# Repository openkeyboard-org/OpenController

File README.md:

# OpenController

OpenController is an open-source wireless keyboard controller designed to be compatible with OpenDongle.

## Firmware

The first firmware target is the WCH CH592F wireless module: a keyboard-side
2.4 GHz link (pairing, connected-mode hopping, HID uplink, persistent
bonding) driven by the keyboard's host MCU over UART, bench-validated
against OpenDongle. See [firmware/README.md](./firmware/README.md) for
toolchain, build, and flashing instructions.

## Hardware

The first hardware implementation is a 10.16 mm x 20.5 mm castellated WCH
CH572D module with OpenDongle's PCB antenna, soldered onto the keyboard PCB
beside the host MCU. It is a first revision that has not been built yet. See [hardware/README.md](./hardware/README.md).

## Repository layout

- `firmware/` — firmware source and related software artifacts.
- `hardware/` — hardware design files and documentation.
- `third_party/` — pinned git submodules used by the firmware.
- `tools/` — development and support tooling.

## Licensing

- Firmware and tools software: [Apache License 2.0](./firmware/LICENSE).
- Hardware designs: [CERN Open Hardware Licence Version 2 - Weakly Reciprocal](./hardware/LICENSE).
- The submodules under `third_party/` contain third-party code under their
  own terms; firmware dependency and derived-file provenance is recorded in
  [`firmware/NOTICE`](./firmware/NOTICE).

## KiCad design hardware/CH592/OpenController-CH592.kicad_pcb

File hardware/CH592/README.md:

# OpenController CH592

OpenController CH592 is a 10.16 mm x 20.5 mm castellated 2.4 GHz wireless module for keyboards, built around the WCH CH592D RISC-V BLE MCU. It has the same outline, castellated pinout, PCB antenna, and 0.8 mm stackup as the [CH572](../CH572/) module, so a host PCB laid out for one takes the other. Like the CH572, it uses the independently created, WCH-informed PCB antenna from [OpenDongle](https://github.com/openkeyboard-org/OpenDongle).

This is the first CH592 revision and no boards have been built yet. The existing OpenController firmware targets the CH592F; it needs a CH592D board profile for this module (see [Known issues](#known-issues-and-next-revision)).

## Design files

| File or directory | Purpose |
| --- | --- |
| `OpenController-CH592.kicad_pro` | KiCad 10 project and design-rule settings |
| `OpenController-CH592.kicad_sch` | Schematic |
| `OpenController-CH592.kicad_pcb` | PCB layout |
| `lib/OpenController.kicad_sym` | Project-owned CH592D symbol |
| `lib/OpenController.pretty/` | Castellated-edge and CH592D QFN-20 footprints drawn for this project, and the antenna footprint copied unchanged from OpenDongle (see [`../NOTICE`](../NOTICE)) |
| `sym-lib-table`, `fp-lib-table` | Portable project-local library configuration |
| `fab/` | Exported outputs: schematic PDF and gerber/NC drill set (see [Fabrication outputs](#fabrication-outputs)) |

Open the project with KiCad 10 or later. The project-owned symbol and footprints resolve through `${KIPRJMOD}` paths in the local library tables. The remaining parts (passives, inductor, crystal, LDO, connector symbol) come from KiCad 10's standard libraries. The schematic and board carry embedded copies of every symbol and footprint, so they open without those libraries, but updating parts from the library needs them installed.

## Host interface

J1 is nine castellated half-holes (1.0 mm drill), three on each of three edges, all on one 0.1 in (2.54 mm) grid so a host can also use standard 0.1 in pin headers. Viewed from the top with the antenna at the bottom, pad 1 is the uppermost pad on the left edge, and the numbering runs counter-clockwise: down the left edge (1-3), up the right edge (4-6), then right to left along the top (7-9). The top silkscreen dot marks pad 1. Pad positions and functions match the CH572 module, except that the CH592D has no reset pin and its USB pins are separate from SWD.

| Pad | Edge | Signal | CH592D pin | Direction | Notes |
| ---: | --- | --- | --- | --- | --- |
| 1 | Left, top | GND | EP | - | |
| 2 | Left, middle | UART_TX | PB13 (8) | out | TXD1 on the UART1 remap, as used by the firmware and OpenBoot |
| 3 | Left, bottom | UART_RX | PB12 (9) | in | RXD1 on the UART1 remap |
| 4 | Right, bottom | NRST | - | - | Not connected: the CH592D has no reset pin |
| 5 | Right, middle | VCC | - | in | 3.3 V to 6.0 V supply into the LDO |
| 6 | Right, top | GND | EP | - | |
| 7 | Top, right | SWDIO | PB14 (7) | bidir | Two-wire debug data (TIO) |
| 8 | Top, middle | SWCLK | PB15 (6) | in | Two-wire debug clock (TCK), also the ROM ISP strap; do not hold low at power-up |
| 9 | Top, left | WAKE | PA11 (1) | out | Host wake line |

The board is 10.16 mm (0.4 in) wide, so the two side rows sit 0.4 in apart. Measured to the hole centres, the top pads are 2.54, 5.08, and 7.62 mm from the left edge, and the side pads are 2.54, 5.08, and 7.62 mm below the top edge. The J1 signals are 3.3 V logic and none is 5 V tolerant; VCC is the supply input and takes 3.3 V to 6.0 V into the LDO. The host PCB must keep copper, ground pour, and metal away from the antenna end of the module.

## Electrical design notes

- VCC feeds U2, a Torex XC6206P332MR-G 3.3 V LDO (pin 1 VSS, pin 2 VOUT, pin 3 VIN). C1 (1 uF) is its input capacitor. Its 6.0 V maximum input covers USB VBUS; from a 3.3 V host rail it runs in dropout, which the CH592D tolerates (1.75 V to 3.6 V supply).
- U2 feeds VIO33/VDD33 (pin 5), the CH592D's only external supply input; VDCID, VDCIA, and VINTA are internal regulator nodes fed from it. C2 (2.2 uF) sits at pin 5 and is both the VDD33 capacitor the datasheet asks for with the DC-DC enabled (2.2 uF or 1 uF) and the LDO output capacitor. OpenDongle CH592 likewise uses a single capacitor there.
- The internal DC-DC converter is fitted. VSW (pin 4) drives L1 (10 uH, the datasheet's recommended value) into VDCID (pin 3). C4 (4.7 uF, the recommended value) decouples VDCID, and VDCIA (pin 16) is tied to VDCID as the datasheet recommends. C5 (470 nF) decouples VINTA (pin 14).
- The DC-DC is off at power-on. The CH592D then supplies VSW directly from VDD33, and L1 passes it through to VDCID. The firmware's `opencontroller-ch592` profile turns the converter on (`KBD_DCDC_ENABLE := 1`). WCH puts the operating current with the DC-DC running at about 60% of the direct-supply figure. OpenDongle CH592 makes the opposite choice: it leaves the DC-DC off and ties VSW straight to VDCID.
- JLC has no Basic inductor suited to the DC-DC: its Basic 10 uH parts (C1035, C1046) are signal inductors rated 3 mA and 15 mA. L1 is a TDK MLZ1608M100WT000, a 0603 multilayer inductor made for DC-DC power lines, with 1.05 ohm DCR and a 90 mA rating in the JLC listing.
- Y1 is a 32 MHz, 8 pF-load crystal on X32MI/X32MO (pins 13 and 12), the same part as the CH572 module. No external load capacitors are fitted; the CH592 provides programmable internal load capacitance (`R8_XT32M_TUNE`), and OpenDongle CH592 also runs an 8 pF crystal on it.
- The RF output (ANT, pin 15) drives the PCB antenna directly, as on OpenDongle.
- GND reaches the CH592D only through the exposed pad (pin 21 in the footprint), which has four 0.6/0.2 mm thermal vias to the bottom ground plane.
- U1's footprint was drawn for this project from the CH592 datasheet's QFN20 drawing (chapter 21: 3.0 +/- 0.1 mm body, 1.9 +/- 0.2 mm exposed pad, 0.25 +/- 0.07 mm leads). KiCad's generic `QFN-20-1EP_3x3mm_P0.4mm_EP1.65x1.65mm` would not do: its lands reach 1.025 mm from the package centre, inside the 1.05 mm edge of a maximum-size CH592D exposed pad. Here the lands run from 1.20 mm to 1.85 mm (0.65 mm x 0.2 mm), 0.15 mm clear of the largest exposed pad. On a nominal 3.0 mm body a longest lead overhangs their inner end by 0.02 mm, and by up to 0.07 mm on a smallest 2.9 mm body. The exposed-pad land is the nominal 1.9 mm. The four thermal vias are built into the footprint, 0.7 mm from the centre along each axis, near the exposed-pad corners. The exposed-pad solder paste is a central window plus four edge windows, 51% of the pad with their rounded corners, each at least 0.175 mm from the via holes, so no paste sits over a via barrel where solder could wick away. The vias are 0.6 mm pads on 0.2 mm drills, which gives the 0.20 mm annular ring JLCPCB asks of plated pad holes. On the top layer their copper merges with the exposed pad: it reaches 0.05 mm beyond the exposed-pad land, under solder mask and at least 0.2 mm from the nearest land, and the paste windows overlap its outer 0.025 mm. The vias are open on the component side, inside the exposed-pad mask opening, and tented on the bottom. TI's thermal-pad guidance (SLMA002) prefers capping them on the component side to limit solder wicking and voiding, but open vias in the exposed pad have worked in OpenKeyboard testing, so they stay open.
- The CH592D's QFN-20 package does not bond out the RST pin, so pad 4 (NRST) is not connected. Reset the module by cycling VCC or over SWD.
- PB15 is the CH592D's ROM ISP strap: held low at power-on, it starts the ROM bootloader. The boot ROM pulls PB15 up, so an open pad 8 boots normally, but a host must not hold pad 8 low during power-up. USB (PB10/PB11) is not brought out, so this module is programmed over two-wire debug rather than ROM ISP. Two-wire debug is enabled from the factory (`CFG_DEBUG_EN`, datasheet Table 2-3), so a WCH-LinkE on pads 7 and 8 programs a blank part, and OpenBoot updates the firmware over the UART after that.
- Unused GPIOs (PA10, PA12 to PA15, PB10, PB11) carry no-connect flags.
- AE1 and J1 are PCB features, not assembly parts. Their footprints are excluded from the BOM and position file.

## Layout notes

- The outline, antenna, ground pours, and via fence are the CH572 module's: the antenna sits along the bottom edge of the 10.16 mm wide board, centred with about 0.58 mm side margins, and both ground pours stop at its inner edge (y = 117.205 mm) behind a 0.5/0.2 mm via fence at 0.75 mm pitch. The two vias beside the antenna's ground pad sit 0.1 mm to 0.15 mm closer to the board edge than on the CH572 to clear the ANT trace.
- The CH592D has ANT, VINTA, X32MI, and X32MO on one side of the package. U1 follows the RF corner of OpenDongle CH592, rotated 90 degrees with the antenna: it sits where U3 sits relative to the antenna feed and via fence there, moved 0.1 mm further from the fence, so that C5 fits in the strip between U1 and the fence without the courtyards overlapping.
- The ANT trace is 0.15 mm wide and about 4.8 mm long (about 4.3 mm on OpenDongle CH592). It runs along U1's pin row and then down beside C5 to the antenna feed.
- Y1 sits at U1's corner on the antenna side. X32MI runs between it and the via fence (0.15 mm, about 7.1 mm) and X32MO into its near pad (about 3.6 mm). The crystal's two ground pads each have a via.
- L1 and C4 sit between U1 and the castellated edge, and VDCIA reaches VDCID around U1's right-hand side. C2 sits beside VDD33, and the LDO and C1 sit between them and the castellated edge.
- Only two signals use the bottom layer: SWDIO from a via at U1's left-hand side, crossing under U1 between its two rows of thermal vias, and WAKE from a via inside the VDCIA loop. Everything else on the bottom layer is ground. SWDIO runs close to the right-hand castellations, so the bottom-layer ground beside pad 6 is a separate piece that joins through pad 6 itself and a stitching via; the rest of the bottom pour is one piece.
- Each castellated pad is 1.5 mm x 3.0 mm and straddles the board edge, leaving 1.5 mm of pad on the board and a 0.25 mm annular ring along the edge. The outermost holes are 2.54 mm (centre) from the corners, so every pad edge is at least 1.79 mm from the adjacent board edge, and hole edges are 1.54 mm apart. See [Known issues](#known-issues-and-next-revision) for JLCPCB's corner guidance.

## Design rules

The board-setup constraints are set to JLCPCB's 1-2 layer, 1 oz capabilities, as on the CH572. The design itself uses larger values (0.2 mm default track and clearance, 0.5/0.2 mm vias).

| Constraint | Setting |
| --- | --- |
| Minimum clearance / track width | 0.10 mm / 0.10 mm |
| Minimum via diameter / annular ring | 0.25 mm / 0.05 mm |
| Minimum through hole | 0.15 mm |
| Hole to hole / hole to copper | 0.20 mm / 0.20 mm |
| Copper to board edge | 0.20 mm (castellated pads are exempt) |
| Silkscreen text height / thickness | 1.0 mm / 0.15 mm |
| Solder mask minimum web | 0.10 mm, 1:1 expansion |

KiCad's board setup has a single hole-to-hole minimum, a single annular-ring minimum (set to JLCPCB's 0.05 mm via value), and no pad-to-silkscreen minimum, so three JLCPCB limits are not checked by DRC: 0.45 mm between plated pad holes, a 0.20 mm annular ring on plated pad holes, and 0.15 mm from pads to silkscreen. The layout meets all three: the closest plated pad holes are U1's thermal vias, 1.2 mm apart edge to edge (the castellations are 1.54 mm apart); the thermal vias have a 0.20 mm ring and the castellations 0.25 mm; and silkscreen stays at least 0.2 mm from every pad opening.

## Design verification

```sh
kicad-cli sch erc --severity-all OpenController-CH592.kicad_sch
kicad-cli pcb drc --severity-all --schematic-parity OpenController-CH592.kicad_pcb
```

ERC reports 0 errors and 0 warnings. DRC reports 0 violations, 0 unconnected items, and 0 schematic parity issues.

## Fabrication outputs

`fab/` holds the exported outputs: the schematic as PDF, and the gerber/NC drill set under `fab/gerbers/`. The KiCad sources remain the design of record; regenerate the exports with KiCad 10 whenever the schematic or layout changes:

```sh
kicad-cli sch export pdf -o fab/OpenController-CH592-schematic.pdf OpenController-CH592.kicad_sch
kicad-cli pcb export gerbers -o fab/gerbers/ \
    -l F.Cu,B.Cu,F.Paste,B.Paste,F.Silkscreen,B.Silkscreen,F.Mask,B.Mask,Edge.Cuts \
    --no-protel-ext --check-zones OpenController-CH592.kicad_pcb
kicad-cli pcb export drill -o fab/gerbers/ --excellon-separate-th \
    --generate-map --map-format gerberx2 OpenController-CH592.kicad_pcb
```

The gerber job file reports 10.21 mm x 20.55 mm and 0.84 mm. The size includes the outline's 0.05 mm line width and the thickness includes both 0.02 mm solder mask layers. Order the board as 10.16 mm x 20.5 mm and 0.8 mm.

Anyone ordering from these files must still pass the stackup, castellation, and antenna requirements below to the fabricator; the gerbers alone do not carry them. JLC-oriented assembly outputs from the Fabrication Toolkit plugin go to `production/`, which stays untracked.

## Fabrication requirements

The antenna is only tuned for this construction. Use these settings unless a revised PCB has been validated:

| Parameter | Requirement |
| --- | --- |
| Layer count | 2 copper layers |
| Finished board size | 10.16 mm x 20.5 mm |
| Finished thickness | 0.8 mm nominal (35 um + 0.73 mm core + 35 um) |
| Material | FR-4 |
| Copper | 1 oz / 35 um outer copper |
| Castellated holes | Yes, on three edges (9 half-holes, 1.0 mm) |
| Surface finish | ENIG recommended for the castellated pads |
| Minimum finished drill | 0.20 mm |
| Minimum track/space used | 0.15 mm track, 0.2 mm clearance |
| Soldermask | Both sides; no soldermask over the castellated pads or antenna conductor |

Preserve the antenna copper, ground edge, board thickness, and via fence exactly, and do not let the fabricator add serial numbers or tooling features in the antenna region. The enclosure and host PCB must not place metal or a ground pour over or directly under the antenna.

## Suggested BOM

The listed LCSC/JLCPCB numbers are suggested assembly parts, not sole-source requirements. Library type is as JLCPCB listed it on 2026-10-25.

| References | Qty | Value / part | Package | Suggested LCSC part | JLC library | Notes |
| --- | ---: | --- | --- | --- | --- | --- |
| U1 | 1 | WCH CH592D | QFN-20, 3 mm x 3 mm, 0.4 mm pitch, exposed pad | C41417128 | Extended | Same part as OpenDongle CH592. Confirm pin-1 orientation and exposed-pad soldering |
| U2 | 1 | Torex XC6206P332MR-G, 3.3 V LDO | SOT-23-3 | C5446 | Basic | 200 mA, 6.0 V maximum input |
| L1 | 1 | 10 uH, TDK MLZ1608M100WT000 | 0603 | C76798 | Extended | DC-DC inductor; JLC's Basic 10 uH parts are 3 mA and 15 mA signal inductors |
| Y1 | 1 | 32 MHz crystal | 2016, 4 pad | C37635332 | Extended | 8 pF load, +/-10 ppm, 40 ohm maximum ESR; same part as the CH572 module. JLC lists no Basic 32 MHz crystal |
| C1 | 1 | 1 uF | 0603 | C15849 | Basic | X5R, 50 V |
| C2 | 1 | 2.2 uF | 0603 | C23630 | Basic | X5R, 16 V |
| C4 | 1 | 4.7 uF | 0603 | C19666 | Basic | X5R, 16 V |
| C5 | 1 | 470 nF | 0603 | C1623 | Basic | X7R, 25 V |

AE1 (PCB antenna) and J1 (castellated edge) are PCB features, not assembly parts.

## Known issues and next revision

- JLCPCB's [castellated PCB design guide](https://jlcpcb.com/blog/castellated-pcbs-introduction-and-design-requirements) recommends at least 3.0 mm (5.0 mm preferred) from a castellated hole to a board corner; the outermost holes here are 2.54 mm (centre) from the corners. That row appears only in the guide's expanded table, not on JLCPCB's capabilities page or in its Chinese design guide, and JLCPCB has built castellated boards with corner holes closer than this. Select castellated holes on three edges when ordering, and expect at most an engineering query.
- The antenna's ground plane is about 10.16 mm x 17 mm here against roughly 10 mm x 13 mm on OpenDongle, and the ANT trace is about 0.5 mm longer than OpenDongle CH592's. Check the match and range on the first boards, soldered to a representative host PCB.
- With VCC at 3.3 V the LDO has almost no headroom. Torex's usage notes ask for stability testing in that condition, so check it on the first boards if hosts will feed the module from a 3.3 V rail.
- The firmware has no CH592D board profile yet. The `opencontroller-ch592` profile already matches this module's UART1 remap (PB13/PB12) and fitted DC-DC inductor. Host wake needs firmware work: the firmware drives its wake line only on PB13, and its boot-time pin park pulls PA11 up until a driver claims it. A profile for this module must drive WAKE on PA11 and leave it out of the park.

## Source attribution

- The 0.8 mm FR-4 antenna footprint is copied from OpenDongle, where it was independently created, informed by the WCH reference antenna published in the [openwch schematic/PCB library](https://github.com/openwch/schpcb_lib); no WCH CAD or artwork file was copied, imported, converted, or traced.

## License

This hardware design, including the antenna implementation described in [`../NOTICE`](../NOTICE), is licensed under the CERN Open Hardware Licence Version 2 - Weakly Reciprocal. See [`LICENSE`](LICENSE).

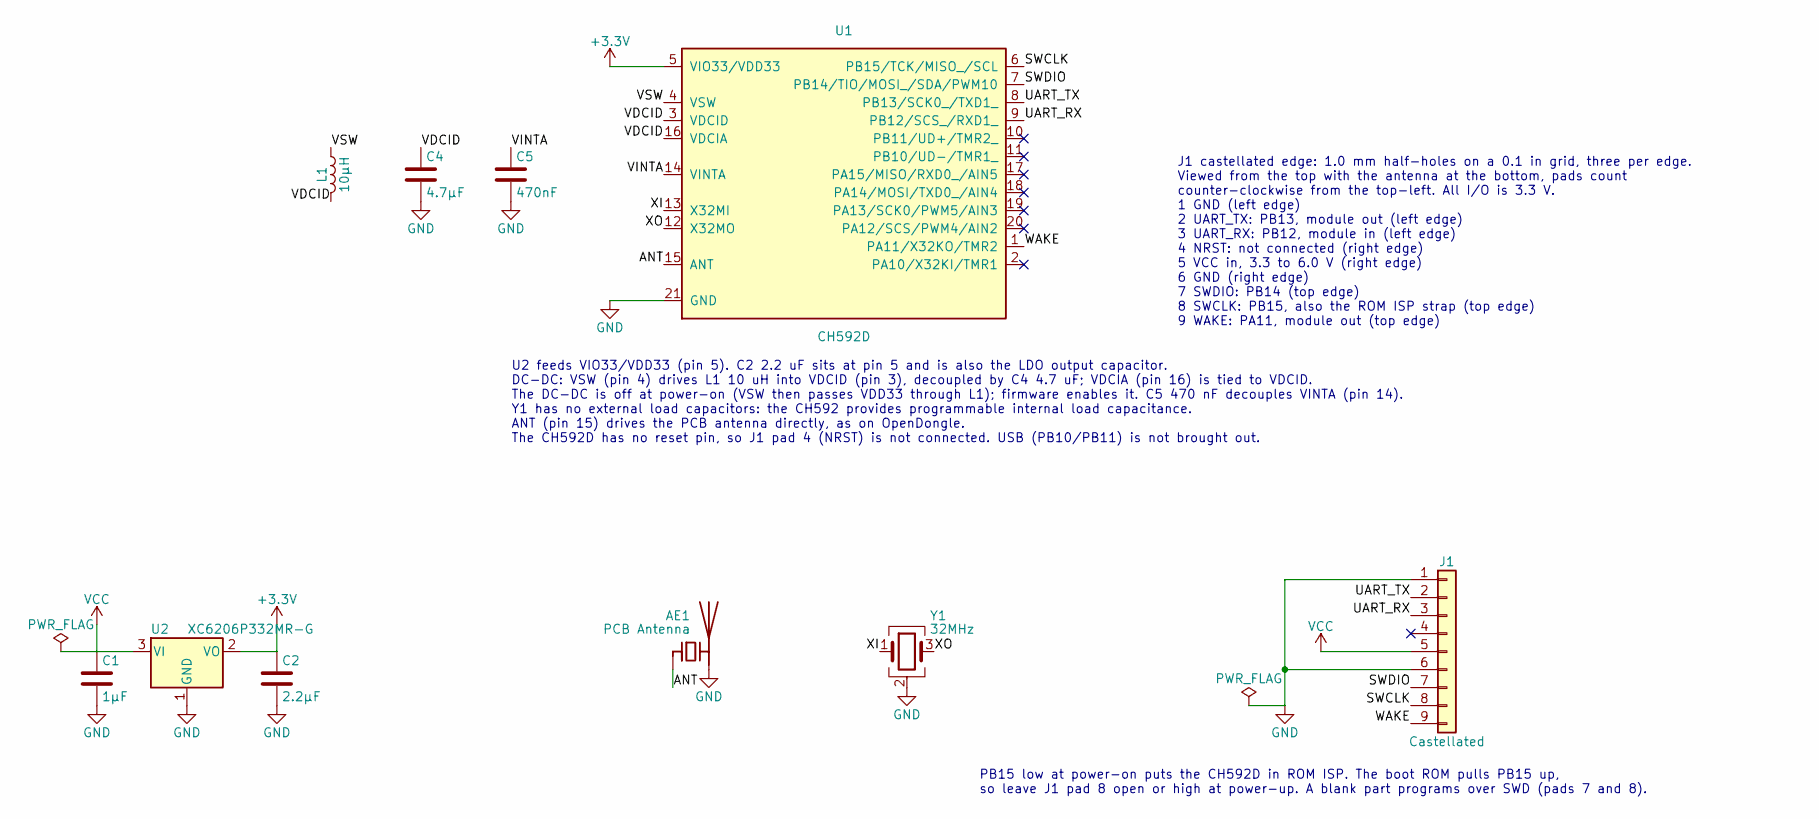
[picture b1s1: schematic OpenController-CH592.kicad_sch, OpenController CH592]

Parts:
AE1: PCB Antenna; ANT-F-2-2.4G-0.8MM-FR4-WCH
C1: 1µF; C_0603_1608Metric; LCSC C15849
C2: 2.2µF; C_0603_1608Metric; LCSC C23630
C4: 4.7µF; C_0603_1608Metric; LCSC C19666
C5: 470nF; C_0603_1608Metric; LCSC C1623
J1: Castellated; Castellated_CH592_10.16x20.5mm
L1: 10µH; L_0603_1608Metric; LCSC C76798
U1: CH592D; QFN-20-1EP_3x3mm_P0.4mm_EP1.9x1.9mm_ThermalVias; LCSC C41417128
U2: XC6206P332MR-G; SOT-23-3; LCSC C5446
Y1: 32MHz; Crystal_SMD_2016-4Pin_2.0x1.6mm; LCSC C37635332

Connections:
+3.3V: C2.1, U1.5 (VIO33/VDD33), U2.2 (VO)
/ANT: AE1.1 (FEED), U1.15 (ANT)
/SWCLK: J1.8, U1.6 (PB15/TCK/MISO_/SCL)
/SWDIO: J1.7, U1.7 (PB14/TIO/MOSI_/SDA/PWM10)
/UART_RX: J1.3, U1.9 (PB12/SCS_/RXD1_)
/UART_TX: J1.2, U1.8 (PB13/SCK0_/TXD1_)
/VDCID: C4.1, L1.2, U1.3 (VDCID), U1.16 (VDCIA)
/VINTA: C5.1, U1.14 (VINTA)
/VSW: L1.1, U1.4 (VSW)
/WAKE: J1.9, U1.1 (PA11/X32KO/TMR2)
/XI: U1.13 (X32MI), Y1.1
/XO: U1.12 (X32MO), Y1.3
GND: AE1.2 (PCB_Trace), C1.2, C2.2, C4.2, C5.2, J1.1, J1.6, U1.21 (GND), U2.1 (GND), Y1.2 (G), Y1.4 (G)
VCC: C1.1, J1.5, U2.3 (VI)

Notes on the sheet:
J1 castellated edge: 1.0 mm half-holes on a 0.1 in grid, three per edge. Viewed from the top with the antenna at the bottom, pads count counter-clockwise from the top-left. All I/O is 3.3 V. 1 GND (left edge) 2 UART_TX: PB13, module out (left edge) 3 UART_RX: PB12, module in (left edge) 4 NRST: not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
PB15 low at power-on puts the CH592D in ROM ISP. The boot ROM pulls PB15 up, so leave J1 pad 8 open or high at power-up. A blank part programs over SWD (pads 7 and 8).
U2 feeds VIO33/VDD33 (pin 5). C2 2.2 uF sits at pin 5 and is also the LDO output capacitor. DC-DC: VSW (pin 4) drives L1 10 uH into VDCID (pin 3), decoupled by C4 4.7 uF; VDCIA (pin 16) is tied to VDCID. The DC-DC is off at power-on (VSW then passes VDD33 through L1); firmware enables it. C5 470 nF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

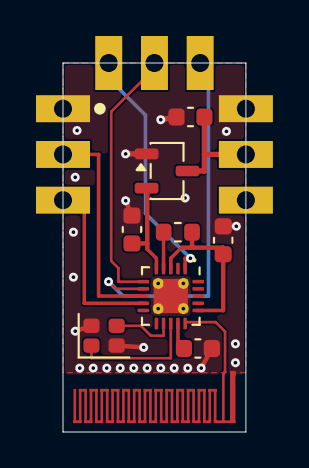
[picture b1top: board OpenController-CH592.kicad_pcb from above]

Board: 2 copper layers, 10.2 x 20.5 mm, 10 parts (0 on the bottom side), 14 nets.

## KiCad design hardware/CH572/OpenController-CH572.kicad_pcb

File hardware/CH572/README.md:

# OpenController CH572

OpenController CH572 is a 10.16 mm x 20.5 mm castellated 2.4 GHz wireless module for keyboards, built around the WCH CH572D RISC-V wireless MCU. It solders onto the keyboard PCB beside the host MCU and talks to it over UART, using the same independently created, WCH-informed PCB antenna and 0.8 mm stackup as [OpenDongle](https://github.com/openkeyboard-org/OpenDongle).

This is the first CH572 revision and no boards have been built yet. The existing OpenController firmware targets the CH592F; a CH572 port is follow-up work.

## Design files

| File or directory | Purpose |
| --- | --- |
| `OpenController-CH572.kicad_pro` | KiCad 10 project and design-rule settings |
| `OpenController-CH572.kicad_sch` | Schematic |
| `OpenController-CH572.kicad_pcb` | PCB layout |
| `lib/OpenController.kicad_sym` | Project-owned CH572D symbol |
| `lib/OpenController.pretty/` | Castellated-edge and CH572D QFN-20 footprints drawn for this project, and the antenna footprint copied unchanged from OpenDongle (see [`../NOTICE`](../NOTICE)) |
| `sym-lib-table`, `fp-lib-table` | Portable project-local library configuration |
| `fab/` | Exported outputs: schematic PDF and gerber/NC drill set (see [Fabrication outputs](#fabrication-outputs)) |

Open the project with KiCad 10 or later. The project-owned symbol and footprints resolve through `${KIPRJMOD}` paths in the local library tables. The remaining parts (passives, crystal, LDO, connector symbol) come from KiCad 10's standard libraries. The schematic and board carry embedded copies of every symbol and footprint, so they open without those libraries, but updating parts from the library needs them installed.

## Host interface

J1 is nine castellated half-holes (1.0 mm drill), three on each of three edges, all on one 0.1 in (2.54 mm) grid so a host can also use standard 0.1 in pin headers. Viewed from the top with the antenna at the bottom, pad 1 is the uppermost pad on the left edge, and the numbering runs counter-clockwise: down the left edge (1-3), up the right edge (4-6), then right to left along the top (7-9). The top silkscreen dot marks pad 1.

| Pad | Edge | Signal | CH572D pin | Direction | Notes |
| ---: | --- | --- | --- | --- | --- |
| 1 | Left, top | GND | EP | - | |
| 2 | Left, middle | UART_TX | PA3 (1) | out | Default UART TXD, as used by OpenBoot's CH57x port |
| 3 | Left, bottom | UART_RX | PA2 (20) | in | Default UART RXD |
| 4 | Right, bottom | NRST | PA8 (10) | in | Default RST pin; reset input is disabled until `CFG_RESET_EN` is set |
| 5 | Right, middle | VCC | - | in | 3.3 V to 6.0 V supply into the LDO |
| 6 | Right, top | GND | EP | - | |
| 7 | Top, right | SWDIO | PA0 (11) | bidir | Also USB D- and UART ISP |
| 8 | Top, middle | SWCLK | PA1 (12) | bidir | Also USB D+ and the ROM boot strap; 100 kOhm pull-down (R1) |
| 9 | Top, left | WAKE | PA4 (13) | out | Host wake line |

The board is 10.16 mm (0.4 in) wide, so the two side rows sit 0.4 in apart. Measured to the hole centres, the top pads are 2.54, 5.08, and 7.62 mm from the left edge, and the side pads are 2.54, 5.08, and 7.62 mm below the top edge. The J1 signals are 3.3 V logic and none is 5 V tolerant; VCC is the supply input and takes 3.3 V to 6.0 V into the LDO. The host PCB must keep copper, ground pour, and metal away from the antenna end of the module.

## Electrical design notes

- VCC feeds U2, a Torex XC6206P332MR-G 3.3 V LDO (pin 1 VSS, pin 2 VOUT, pin 3 VIN). C1 (1 uF) is its input capacitor. Its 6.0 V maximum input covers USB VBUS; from a 3.3 V host rail it runs in dropout, which the CH572 tolerates (2.0 V to 3.6 V low-voltage supply mode).
- The CH572D runs in single 3.3 V supply mode: V5 (pin 8) and VIO33 (pin 7) are tied to VDD33 (pin 6), as datasheet Table 1-1 allows. The three pins are joined at the pads. C3 (100 nF) sits at pin 6 and C2 (2.2 uF) is both the VDD33 bulk capacitor and the LDO output capacitor, matching the datasheet's 2.2 uF plus 0.1 uF requirement.
- Y1 is a 32 MHz, 8 pF-load crystal on XI/XO (pins 3 and 2). No external load capacitors are fitted; the CH572 provides programmable internal load capacitance.
- The RF output (ANT, pin 5) drives the PCB antenna directly, as on OpenDongle.
- GND reaches the CH572D only through the exposed pad (pin 21 in the footprint, pin 0 in the datasheet), which has four 0.6/0.2 mm thermal vias to the bottom ground plane.
- U1's footprint was drawn for this project from the CH572 datasheet's QFN20 drawing (3.0 +/- 0.1 mm body, 1.8 +/- 0.2 mm exposed pad, 0.35 +/- 0.12 mm leads). The lands run from 1.15 mm to 1.85 mm from the package centre (0.7 mm x 0.2 mm), 0.15 mm clear of the largest exposed pad; they start where a nominal lead ends, and a longest lead on a smallest body overhangs their inner end by up to 0.17 mm. The exposed-pad land is the nominal 1.8 mm, with the thermal vias built in 0.65 mm from the centre along each axis, near the pad corners. The exposed-pad solder paste is a central window plus four edge windows, 51% of the pad with their rounded corners, each at least 0.19 mm from the via holes, so no paste sits over a via barrel where solder could wick away. The vias are 0.6 mm pads on 0.2 mm drills, which gives the 0.20 mm annular ring JLCPCB asks of plated pad holes. On the top layer their copper merges with the exposed pad: it reaches 0.05 mm beyond the exposed-pad land, under solder mask and at least 0.2 mm from the nearest land, and the paste windows overlap its outer 0.01 mm. The vias are open on the component side, inside the exposed-pad mask opening, and tented on the bottom. TI's thermal-pad guidance (SLMA002) prefers capping them on the component side to limit solder wicking and voiding, but open vias in the exposed pad have worked in OpenKeyboard testing, so they stay open.
- NRST uses PA8, the factory-default reset pin (datasheet Table 2-3: `CFG_RST_PIN_EN` = 0). The reset input itself is off by default; set `CFG_RESET_EN` in the configuration bits to use it.
- PA1 is the ROM boot strap: PA1 high with PA0 low at power-on enters USB/UART ISP. R1 holds PA1 low when pad 8 is left open, so a cold power-up never parks in the bootloader by accident. A WCH-LinkE on pads 7/8 or the D+ pull-up "boot cable" still overrides it.
- R1 is a deliberate trade-off against USB. USB 2.0 full speed asks for at least 300 kOhm input impedance on D+ (Table 7-7), and R1 is 100 kOhm. At 300 kOhm, the CH572's worst-case floating-input leakage (3 uA) would put PA1 exactly at VIL max (0.9 V) and the strap would no longer be guaranteed; at 100 kOhm it sits at 0.3 V or below. USB on this module is only an ISP path, and R1 moves the D+ idle level from about 3.0 V to 2.96 V against a 2.0 V threshold.
- Unused GPIOs (PA5, PA6, PA7, PA9, PA10, PA11) and the two NC pins carry no-connect flags.
- AE1 and J1 are PCB features, not assembly parts. Their footprints are excluded from the BOM and position file.

## Layout notes

- The antenna sits along the bottom edge, centred on a 10.16 mm wide board with about 0.58 mm side margins. That is 0.16 mm wider than OpenDongle, so the side castellations sit 0.4 in apart; the ground edge the antenna sees is 1.6% wider.
- The ground pours on both layers stop at the antenna's inner edge (y = 117.205 mm), and a 0.5/0.2 mm via fence runs about 0.25 mm inside that edge (via centres at y = 116.95 mm) at 0.75 mm pitch, following OpenDongle.
- The ANT trace is 0.15 mm wide and 2.7 mm long, from U1 pin 5 to the antenna feed.
- U1 is rotated so that ANT, XI and XO face the antenna. The crystal sits beside U1, and UART_TX/UART_RX drop to the bottom layer through two vias at U1's corner.
- The bottom layer carries the six castellated signal runs; everything else is ground.
- Each castellated pad is 1.5 mm x 3.0 mm and straddles the board edge, leaving 1.5 mm of pad on the board and a 0.25 mm annular ring along the edge. The outermost holes are 2.54 mm (centre) from the corners, so every pad edge is at least 1.79 mm from the adjacent board edge, and hole edges are 1.54 mm apart. See [Known issues](#known-issues-and-next-revision) for JLCPCB's corner guidance.

## Design rules

The board-setup constraints are set to JLCPCB's 1-2 layer, 1 oz capabilities. The design itself uses larger values (0.2 mm default track and clearance, 0.5/0.2 mm vias).

| Constraint | Setting |
| --- | --- |
| Minimum clearance / track width | 0.10 mm / 0.10 mm |
| Minimum via diameter / annular ring | 0.25 mm / 0.05 mm |
| Minimum through hole | 0.15 mm |
| Hole to hole / hole to copper | 0.20 mm / 0.20 mm |
| Copper to board edge | 0.20 mm (castellated pads are exempt) |
| Silkscreen text height / thickness | 1.0 mm / 0.15 mm |
| Solder mask minimum web | 0.10 mm, 1:1 expansion |

KiCad's board setup has a single hole-to-hole minimum, a single annular-ring minimum (set to JLCPCB's 0.05 mm via value), and no pad-to-silkscreen minimum, so three JLCPCB limits are not checked by DRC: 0.45 mm between plated pad holes, a 0.20 mm annular ring on plated pad holes, and 0.15 mm from pads to silkscreen. The layout meets all three: the closest plated pad holes are U1's thermal vias, 1.1 mm apart edge to edge (the castellations are 1.54 mm apart); the thermal vias have a 0.20 mm ring and the castellations 0.25 mm; and silkscreen stays at least 0.2 mm from every pad opening.

## Design verification

```sh
kicad-cli sch erc --severity-all OpenController-CH572.kicad_sch
kicad-cli pcb drc --severity-all --schematic-parity OpenController-CH572.kicad_pcb
```

ERC reports 0 errors and 0 warnings. DRC reports 0 violations, 0 unconnected items, and 0 schematic parity issues.

## Fabrication outputs

`fab/` holds the exported outputs: the schematic as PDF, and the gerber/NC drill set under `fab/gerbers/`. The KiCad sources remain the design of record; regenerate the exports with KiCad 10 whenever the schematic or layout changes:

```sh
kicad-cli sch export pdf -o fab/OpenController-CH572-schematic.pdf OpenController-CH572.kicad_sch
kicad-cli pcb export gerbers -o fab/gerbers/ \
    -l F.Cu,B.Cu,F.Paste,B.Paste,F.Silkscreen,B.Silkscreen,F.Mask,B.Mask,Edge.Cuts \
    --no-protel-ext --check-zones OpenController-CH572.kicad_pcb
kicad-cli pcb export drill -o fab/gerbers/ --excellon-separate-th \
    --generate-map --map-format gerberx2 OpenController-CH572.kicad_pcb
```

The gerber job file reports 10.21 mm x 20.55 mm and 0.84 mm. The size includes the outline's 0.05 mm line width and the thickness includes both 0.02 mm solder mask layers. Order the board as 10.16 mm x 20.5 mm and 0.8 mm.

Anyone ordering from these files must still pass the stackup, castellation, and antenna requirements below to the fabricator; the gerbers alone do not carry them. JLC-oriented assembly outputs from the Fabrication Toolkit plugin go to `production/`, which stays untracked.

## Fabrication requirements

The antenna is only tuned for this construction. Use these settings unless a revised PCB has been validated:

| Parameter | Requirement |
| --- | --- |
| Layer count | 2 copper layers |
| Finished board size | 10.16 mm x 20.5 mm |
| Finished thickness | 0.8 mm nominal (35 um + 0.73 mm core + 35 um) |
| Material | FR-4 |
| Copper | 1 oz / 35 um outer copper |
| Castellated holes | Yes, on three edges (9 half-holes, 1.0 mm) |
| Surface finish | ENIG recommended for the castellated pads |
| Minimum finished drill | 0.20 mm |
| Minimum track/space used | 0.15 mm track, 0.2 mm clearance |
| Soldermask | Both sides; no soldermask over the castellated pads or antenna conductor |

Preserve the antenna copper, ground edge, board thickness, and via fence exactly, and do not let the fabricator add serial numbers or tooling features in the antenna region. The enclosure and host PCB must not place metal or a ground pour over or directly under the antenna.

## Suggested BOM

The listed LCSC/JLCPCB numbers are suggested assembly parts, not sole-source requirements. Library type is as JLCPCB listed it on 2026-10-25.

| References | Qty | Value / part | Package | Suggested LCSC part | JLC library | Notes |
| --- | ---: | --- | --- | --- | --- | --- |
| U1 | 1 | WCH CH572D | QFN-20, 3 mm x 3 mm, 0.4 mm pitch, exposed pad | C46597863 | Extended | Confirm pin-1 orientation and exposed-pad soldering |
| U2 | 1 | Torex XC6206P332MR-G, 3.3 V LDO | SOT-23-3 | C5446 | Basic | 200 mA, 6.0 V maximum input |
| Y1 | 1 | 32 MHz crystal | 2016, 4 pad | C37635332 | Extended | 8 pF load, +/-10 ppm, 40 ohm maximum ESR; same part as OpenDongle CH570. JLC lists no Basic 32 MHz crystal |
| C1 | 1 | 1 uF | 0603 | C15849 | Basic | X5R, 50 V |
| C2 | 1 | 2.2 uF | 0603 | C23630 | Basic | X5R, 16 V |
| C3 | 1 | 100 nF | 0603 | C14663 | Basic | X7R, 50 V |
| R1 | 1 | 100 kOhm, 1% | 0603 | C25803 | Basic | PA1 boot-strap pull-down |

AE1 (PCB antenna) and J1 (castellated edge) are PCB features, not assembly parts.

## Known issues and next revision

- JLCPCB's [castellated PCB design guide](https://jlcpcb.com/blog/castellated-pcbs-introduction-and-design-requirements) recommends at least 3.0 mm (5.0 mm preferred) from a castellated hole to a board corner; the outermost holes here are 2.54 mm (centre) from the corners. That row appears only in the guide's expanded table, not on JLCPCB's capabilities page or in its Chinese design guide, and JLCPCB has built castellated boards with corner holes closer than this. Select castellated holes on three edges when ordering, and expect at most an engineering query.
- The antenna's ground plane is about 10.16 mm x 17 mm here against roughly 10 mm x 13 mm on OpenDongle. Check the match and range on the first boards, soldered to a representative host PCB.
- With VCC at 3.3 V the LDO has almost no headroom. Torex's usage notes ask for stability testing in that condition, so check it on the first boards if hosts will feed the module from a 3.3 V rail.
- The firmware has no CH572 board profile yet. The OpenBoot CH57x port already uses the PA3/PA2 UART mapping that J1 carries.

## Source attribution

- The 0.8 mm FR-4 antenna footprint is copied from OpenDongle, where it was independently created, informed by the WCH reference antenna published in the [openwch schematic/PCB library](https://github.com/openwch/schpcb_lib); no WCH CAD or artwork file was copied, imported, converted, or traced.

## License

This hardware design, including the antenna implementation described in [`../NOTICE`](../NOTICE), is licensed under the CERN Open Hardware Licence Version 2 - Weakly Reciprocal. See [`LICENSE`](LICENSE).

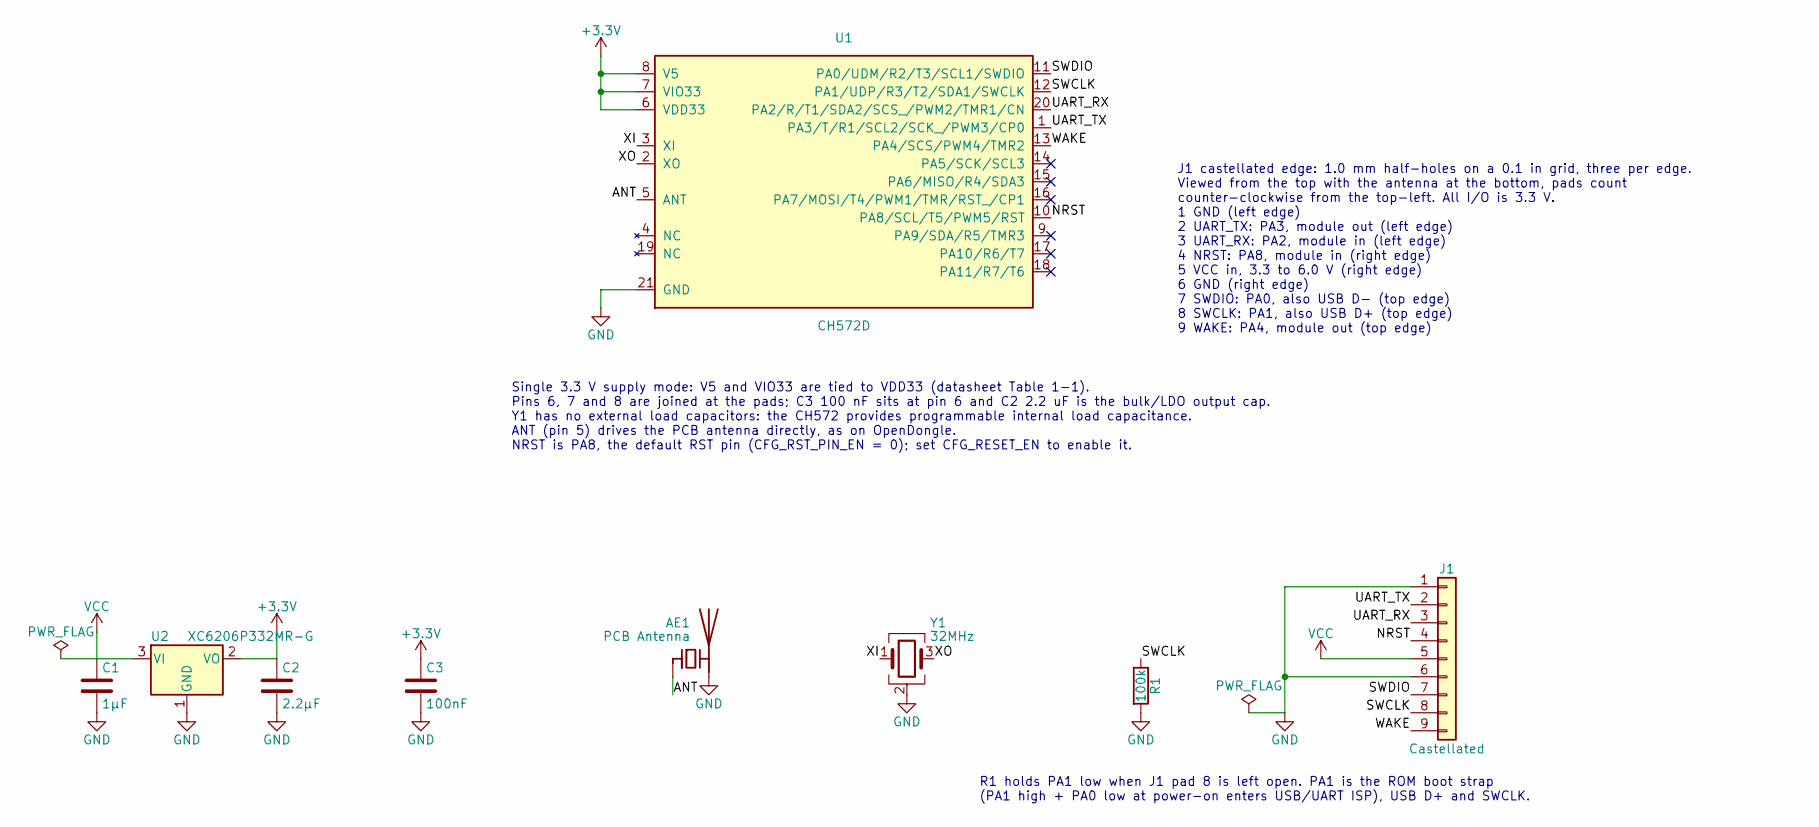
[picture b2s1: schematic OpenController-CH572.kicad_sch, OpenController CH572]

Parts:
AE1: PCB Antenna; ANT-F-2-2.4G-0.8MM-FR4-WCH
C1: 1µF; C_0603_1608Metric; LCSC C15849
C2: 2.2µF; C_0603_1608Metric; LCSC C23630
C3: 100nF; C_0603_1608Metric; LCSC C14663
J1: Castellated; Castellated_CH572_10.16x20.5mm
R1: 100k; R_0603_1608Metric; LCSC C25803
U1: CH572D; CH572D_QFN-20_3x3mm_P0.4mm_EP1.8mm_ThermalVias; LCSC C46597863
U2: XC6206P332MR-G; SOT-23-3; LCSC C5446
Y1: 32MHz; Crystal_SMD_2016-4Pin_2.0x1.6mm; LCSC C37635332

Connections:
+3.3V: C2.1, C3.1, U1.6 (VDD33), U1.7 (VIO33), U1.8 (V5), U2.2 (VO)
/ANT: AE1.1 (FEED), U1.5 (ANT)
/NRST: J1.4, U1.10 (PA8/SCL/T5/PWM5/RST)
/SWCLK: J1.8, R1.1, U1.12 (PA1/UDP/R3/T2/SDA1/SWCLK)
/SWDIO: J1.7, U1.11 (PA0/UDM/R2/T3/SCL1/SWDIO)
/UART_RX: J1.3, U1.20 (PA2/R/T1/SDA2/SCS_/PWM2/TMR1/CN)
/UART_TX: J1.2, U1.1 (PA3/T/R1/SCL2/SCK_/PWM3/CP0)
/WAKE: J1.9, U1.13 (PA4/SCS/PWM4/TMR2)
/XI: U1.3 (XI), Y1.1
/XO: U1.2 (XO), Y1.3
GND: AE1.2 (PCB_Trace), C1.2, C2.2, C3.2, J1.1, J1.6, R1.2, U1.21 (GND), U2.1 (GND), Y1.2 (G), Y1.4 (G)
VCC: C1.1, J1.5, U2.3 (VI)

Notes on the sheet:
Single 3.3 V supply mode: V5 and VIO33 are tied to VDD33 (datasheet Table 1-1). Pins 6, 7 and 8 are joined at the pads; C3 100 nF sits at pin 6 and C2 2.2 uF is the bulk/LDO output cap. Y1 has no external load capacitors: the CH572 provides programmable internal load capacitance. ANT (pin 5) drives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
R1 holds PA1 low when J1 pad 8 is left open. PA1 is the ROM boot strap (PA1 high + PA0 low at power-on enters USB/UART ISP), USB D+ and SWCLK.
J1 castellated edge: 1.0 mm half-holes on a 0.1 in grid, three per edge. Viewed from the top with the antenna at the bottom, pads count counter-clockwise from the top-left. All I/O is 3.3 V. 1 GND (left edge) 2 UART_TX: PA3, module out (left edge) 3 UART_RX: PA2, module in (left edge) 4 NRST: PA8, 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

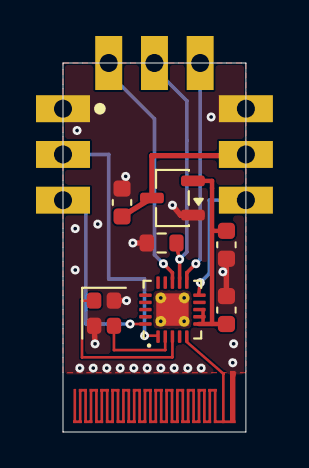
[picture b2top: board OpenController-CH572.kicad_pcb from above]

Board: 2 copper layers, 10.2 x 20.5 mm, 9 parts (0 on the bottom side), 12 nets.

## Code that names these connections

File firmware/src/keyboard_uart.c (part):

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
#if KBD_HOST_WAKE
#if KBD_UART1_REMAP
#error "KBD_HOST_WAKE drives PB13, which the UART1 remap uses as TXD1"
#endif
#include "host_wake.h"
/* PB13: TXD1 under the UART1 remap, the CHWAKE line on the MK65MX. */
#define KBD_CHWAKE_PIN bTXD1_
static host_wake_t host_wake;
static uint8_t chwake_level;
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    GPIOB_ModeCfg(bTXD1_, GPIO_ModeOut_PP_5mA);
    GPIOB_ModeCfg(bRXD1_, GPIO_ModeIN_PU);
#else
    /* MK65MX uses UART1's default PA8/PA9 mapping.  PB13 is CHWAKE on that
     * board, pulled down at the host (STM32 PA1).  A KBD_HOST_WAKE build
     * drives it push-pull from here on, low until a frame is queued, so a
     * reset module never leaves it unexplained; any other build leaves it a
     * FLOATING input, since a pull-up against the host's pull-down would
     * burn current for nothing.  PB12 is genuinely unconnected there and
     * keeps the input-pull-up park from main(); floating it leaves a CMOS
     * input mid-rail burning crossbar current. */
#if KBD_HOST_WAKE
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

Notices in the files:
firmware/src/keyboard_uart.c:
Copyright 2026 Eric Molitor (EMulator)
SPDX-License-Identifier: Apache-2.0
hardware/CH572/OpenController-CH572.kicad_pcb:
CERN-OHL-W CERN Open Hardware Licence Version 2 - Weakly Reciprocal
